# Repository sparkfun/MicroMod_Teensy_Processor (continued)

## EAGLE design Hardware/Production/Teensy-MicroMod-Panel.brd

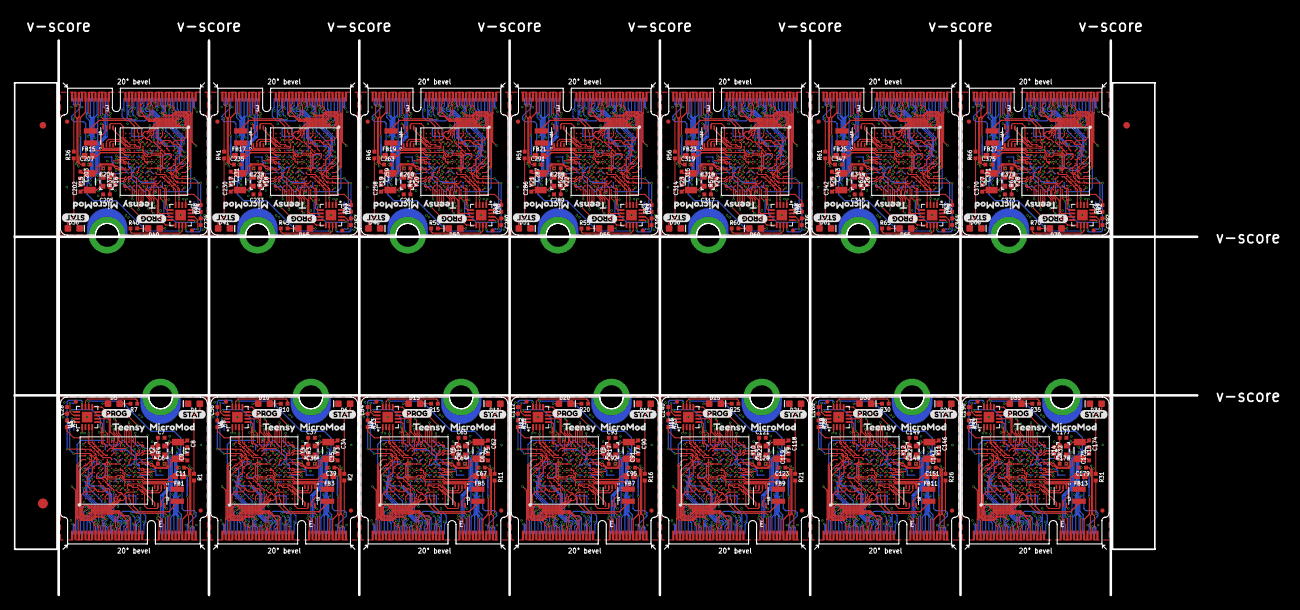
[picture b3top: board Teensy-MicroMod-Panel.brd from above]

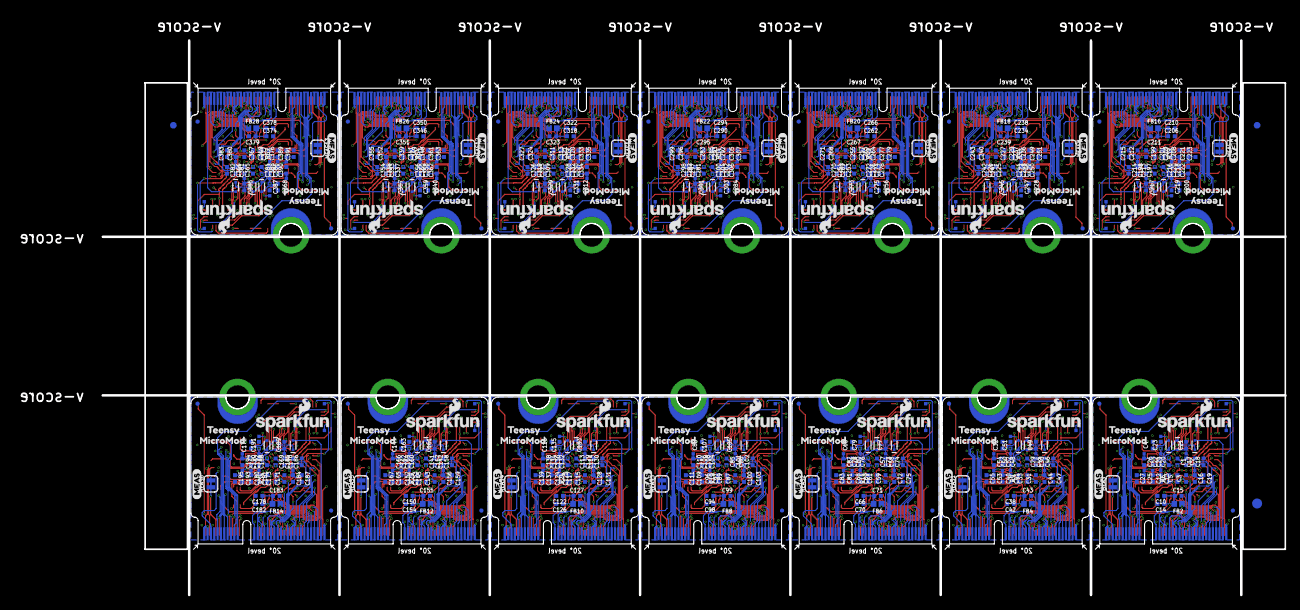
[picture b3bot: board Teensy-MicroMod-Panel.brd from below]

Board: 4 copper layers, 177.1 x 83.1 mm, 986 parts (619 on the bottom side), 1218 nets.

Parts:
C1, C11, C29, C39, C57, C67, C85, C95, C113, C123, C141, C151, C169, C179, C197, C207, C225, C235, C253, C263, C281, C291, C309, C319, C337, C347, C365, C375: 2.2uF; 0402-TIGHT
C2, C14, C18, C26, C27, C30, C42, C46, C54, C55, C58, C70, C74, C82, C83, C86, C98, C102, C110, C111, C114, C126, C130, C138, C139, C142, C154, C158, C166, C167, C170, C182, C186, C194, C195, C198, C210, C214, C222, C223, C226, C238, C242, C250, C251, C254, C266, C270, C278, C279, C282, C294, C298, C306, C307, C310, C322, C326, C334, C335, C338, C350, C354, C362, C363, C366, C378, C382, C390, C391: 4.7uF; 0402-TIGHT
C3, C4, C12, C13, C15, C17, C20, C22, C23, C24, C25, C28, C31, C32, C40, C41, C43, C45, C48, C50, C51, C52, C53, C56, C59, C60, C68, C69, C71, C73, C76, C78, C79, C80, C81, C84, C87, C88, C96, C97, C99, C101, C104, C106, C107, C108, C109, C112, C115, C116, C124, C125, C127, C129, C132, C134, C135, C136, C137, C140, C143, C144, C152, C153, C155, C157, C160, C162, C163, C164, C165, C168, C171, C172, C180, C181, C183, C185, C188, C190, C191, C192, C193, C196, C199, C200, C208, C209, C211, C213, C216, C218, C219, C220, C221, C224, C227, C228, C236, C237, C239, C241, C244, C246, C247, C248, C249, C252, C255, C256, C264, C265, C267, C269, C272, C274, C275, C276, C277, C280, C283, C284, C292, C293, C295, C297, C300, C302, C303, C304, C305, C308, C311, C312, C320, C321, C323, C325, C328, C330, C331, C332, C333, C336, C339, C340, C348, C349, C351, C353, C356, C358, C359, C360, C361, C364, C367, C368, C376, C377, C379, C381, C384, C386, C387, C388, C389, C392: 0.22uF; 0402-TIGHT
C5, C16, C33, C44, C61, C72, C89, C100, C117, C128, C145, C156, C173, C184, C201, C212, C229, C240, C257, C268, C285, C296, C313, C324, C341, C352, C369, C380: 10nF; 0402-TIGHT
C6, C7, C36, C37, C64, C65, C92, C93, C120, C121, C148, C149, C176, C177, C204, C205, C232, C233, C260, C261, C288, C289, C316, C317, C344, C345, C372, C373: 12pF; 0402-TIGHT
C8, C9, C34, C35, C62, C63, C90, C91, C118, C119, C146, C147, C174, C175, C202, C203, C230, C231, C258, C259, C286, C287, C314, C315, C342, C343, C370, C371: 20pF; 0402-TIGHT
C10, C19, C21, C38, C47, C49, C66, C75, C77, C94, C103, C105, C122, C131, C133, C150, C159, C161, C178, C187, C189, C206, C215, C217, C234, C243, C245, C262, C271, C273, C290, C299, C301, C318, C327, C329, C346, C355, C357, C374, C383, C385: 10uF; 0402-TIGHT
D1, D6, D11, D16, D21, D26, D31, D36, D41, D46, D51, D56, D61, D66: BLUE; LED-0603
D2, D7, D12, D17, D22, D27, D32, D37, D42, D47, D52, D57, D62, D67: 120mA370mV; SOD-523
D3, D4, D8, D9, D13, D14, D18, D19, D23, D24, D28, D29, D33, D34, D38, D39, D43, D44, D48, D49, D53, D54, D58, D59, D63, D64, D68, D69: 120mA/370mV; SOD-523
D5, D10, D15, D20, D25, D30, D35, D40, D45, D50, D55, D60, D65, D70: Yellow; LED-0603
E$1, E$2, E$3, E$4: FIDUCIAL-1X2
E$5, E$6: FIDUCIAL-1.5X3
FB1, FB2, FB3, FB4, FB5, FB6, FB7, FB8, FB9, FB10, FB11, FB12, FB13, FB14, FB15, FB16, FB17, FB18, FB19, FB20, FB21, FB22, FB23, FB24, FB25, FB26, FB27, FB28: 120Ω; 0402
FD1, FD2, FD3, FD4, FD5, FD6, FD7, FD8, FD9, FD10, FD11, FD12, FD13, FD14, FD15, FD16, FD17, FD18, FD19, FD20, FD21, FD22, FD23, FD24, FD25, FD26, FD27, FD28, FD29, FD30, FD31, FD32, FD33, FD34, FD35, FD36, FD37, FD38, FD39, FD40, FD41, FD42, FD43, FD44, FD45, FD46, FD47, FD48, FD49, FD50, FD51, FD52, FD53, FD54, FD55, FD56: FIDUCIALUFIDUCIAL; FIDUCIAL-MICRO
J1, J2, J3, J4, J5, J6, J7, J8, J9, J10, J11, J12, J13, J14: MICROMOD-2222; M.2-CARD-E-22
L1, L2, L3, L4, L5, L6, L7, L8, L9, L10, L11, L12, L13, L14: 4.7μH; 1008(2520)
LOGO1, LOGO2, LOGO3, LOGO4, LOGO5, LOGO6, LOGO7, LOGO8, LOGO9, LOGO10, LOGO11, LOGO12, LOGO13, LOGO14: SFE_LOGO_NAME_FLAME.1_INCH; SFE_LOGO_NAME_FLAME_.1
MEAS, MEAS1, MEAS2, MEAS3, MEAS4, MEAS5, MEAS6, MEAS7, MEAS8, MEAS9, MEAS10, MEAS11, MEAS12, MEAS13: SMT-JUMPER_2_NC_TRACE_SILK
R1, R2, R7, R10, R11, R15, R16, R20, R21, R25, R26, R30, R31, R35, R36, R40, R41, R45, R46, R50, R51, R55, R56, R60, R61, R65, R66, R70: 1k; 0402-TIGHT
R3, R4, R12, R17, R22, R27, R32, R37, R42, R47, R52, R57, R62, R67: 2.2M; 0402-TIGHT
R5, R6, R8, R9, R13, R14, R18, R19, R23, R24, R28, R29, R33, R34, R38, R39, R43, R44, R48, R49, R53, R54, R58, R59, R63, R64, R68, R69: 100k; 0402-TIGHT
TP1, TP2, TP21, TP31, TP41, TP51, TP61, TP71, TP81, TP91, TP101, TP111, TP121, TP131: 32kHz Test; PAD.02X.02
TP3, TP4, TP5, TP6, TP7, TP8, TP9, TP10, TP11, TP12, TP13, TP14, TP15, TP16, TP17, TP18, TP19, TP20, TP22, TP23, TP24, TP25, TP26, TP27, TP28, TP29, TP30, TP32, TP33, TP34, TP35, TP36, TP37, TP38, TP39, TP40, TP42, TP43, TP44, TP45, TP46, TP47, TP48, TP49, TP50, TP52, TP53, TP54, TP55, TP56, TP57, TP58, TP59, TP60, TP62, TP63, TP64, TP65, TP66, TP67, TP68, TP69, TP70, TP72, TP73, TP74, TP75, TP76, TP77, TP78, TP79, TP80, TP82, TP83, TP84, TP85, TP86, TP87, TP88, TP89, TP90, TP92, TP93, TP94, TP95, TP96, TP97, TP98, TP99, TP100, TP102, TP103, TP104, TP105, TP106, TP107, TP108, TP109, TP110, TP112, TP113, TP114, TP115, TP116, TP117, TP118, TP119, TP120, TP122, TP123, TP124, TP125, TP126, TP127, TP128, TP129, TP130, TP132, TP133, TP134, TP135, TP136, TP137, TP138, TP139, TP140: PAD.02X.02
U1, U4, U7, U10, U13, U16, U19, U22, U25, U28, U31, U34, U37, U40: IMXRT1062DV10X10; IMXRT1062
U2, U5, U8, U11, U14, U17, U20, U23, U26, U29, U32, U35, U38, U41: W25QXX; USON-8
U3, U6, U9, U12, U15, U18, U21, U24, U27, U30, U33, U36, U39, U42: MKL02Z32VFG4; QFN-16
U$1, U$3, U$9, U$12, U$16, U$19, U$23, U$26, U$30, U$33, U$37, U$40, U$44, U$47, U$51, U$54, U$58, U$61, U$65, U$68, U$72, U$75, U$79, U$82, U$86, U$89, U$93, U$96: TEENSY2
U$2, U$5, U$8, U$13, U$15, U$20, U$22, U$27, U$29, U$34, U$36, U$41, U$43, U$48, U$50, U$55, U$57, U$62, U$64, U$69, U$71, U$76, U$78, U$83, U$85, U$90, U$92, U$97: MICROMOD0
U$4, U$11, U$18, U$25, U$32, U$39, U$46, U$53, U$60, U$67, U$74, U$81, U$88, U$95: PROG_32
U$6, U$10, U$17, U$24, U$31, U$38, U$45, U$52, U$59, U$66, U$73, U$80, U$87, U$94: STAT_32
U$7, U$14, U$21, U$28, U$35, U$42, U$49, U$56, U$63, U$70, U$77, U$84, U$91, U$98: MEAS_32
Y1, Y3, Y5, Y7, Y9, Y11, Y13, Y15, Y17, Y19, Y21, Y23, Y25, Y27: 32.768kHz; CRYSTAL-SMD-3.2X1.5MM
Y2, Y4, Y6, Y8, Y10, Y12, Y14, Y16, Y18, Y20, Y22, Y24, Y26, Y28: 24MHz; CRYSTAL-SMD-2.0X1.6MM

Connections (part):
3.3V: C1.1, C2.1, C3.1, C4.1, C5.1, C28.1, D2.A, D5.A, FB2.1, J1.2, J1.4, J1.74, R6.1, U1.E6, U1.E9, U1.F5, U1.F10, U1.J6, U1.J10, U1.K4, U1.K5, U1.N14, U1.P12, U2.8, U3.1
3.3V1: C29.1, C30.1, C31.1, C32.1, C33.1, C56.1, D7.A, D10.A, FB4.1, J2.2, J2.4, J2.74, R9.1, U4.E6, U4.E9, U4.F5, U4.F10, U4.J6, U4.J10, U4.K4, U4.K5, U4.N14, U4.P12, U5.8, U6.1
3.3V2: C57.1, C58.1, C59.1, C60.1, C61.1, C84.1, D12.A, D15.A, FB6.1, J3.2, J3.4, J3.74, R14.1, U7.E6, U7.E9, U7.F5, U7.F10, U7.J6, U7.J10, U7.K4, U7.K5, U7.N14, U7.P12, U8.8, U9.1
3.3V3: C85.1, C86.1, C87.1, C88.1, C89.1, C112.1, D17.A, D20.A, FB8.1, J4.2, J4.4, J4.74, R19.1, U10.E6, U10.E9, U10.F5, U10.F10, U10.J6, U10.J10, U10.K4, U10.K5, U10.N14, U10.P12, U11.8, U12.1
3.3V4: C113.1, C114.1, C115.1, C116.1, C117.1, C140.1, D22.A, D25.A, FB10.1, J5.2, J5.4, J5.74, R24.1, U13.E6, U13.E9, U13.F5, U13.F10, U13.J6, U13.J10, U13.K4, U13.K5, U13.N14, U13.P12, U14.8, U15.1
3.3V5: C141.1, C142.1, C143.1, C144.1, C145.1, C168.1, D27.A, D30.A, FB12.1, J6.2, J6.4, J6.74, R29.1, U16.E6, U16.E9, U16.F5, U16.F10, U16.J6, U16.J10, U16.K4, U16.K5, U16.N14, U16.P12, U17.8, U18.1
3.3V6: C169.1, C170.1, C171.1, C172.1, C173.1, C196.1, D32.A, D35.A, FB14.1, J7.2, J7.4, J7.74, R34.1, U19.E6, U19.E9, U19.F5, U19.F10, U19.J6, U19.J10, U19.K4, U19.K5, U19.N14, U19.P12, U20.8, U21.1
3.3V7: C197.1, C198.1, C199.1, C200.1, C201.1, C224.1, D37.A, D40.A, FB16.1, J8.2, J8.4, J8.74, R39.1, U22.E6, U22.E9, U22.F5, U22.F10, U22.J6, U22.J10, U22.K4, U22.K5, U22.N14, U22.P12, U23.8, U24.1
3.3V8: C225.1, C226.1, C227.1, C228.1, C229.1, C252.1, D42.A, D45.A, FB18.1, J9.2, J9.4, J9.74, R44.1, U25.E6, U25.E9, U25.F5, U25.F10, U25.J6, U25.J10, U25.K4, U25.K5, U25.N14, U25.P12, U26.8, U27.1
3.3V9: C253.1, C254.1, C255.1, C256.1, C257.1, C280.1, D47.A, D50.A, FB20.1, J10.2, J10.4, J10.74, R49.1, U28.E6, U28.E9, U28.F5, U28.F10, U28.J6, U28.J10, U28.K4, U28.K5, U28.N14, U28.P12, U29.8, U30.1
3.3V10: C281.1, C282.1, C283.1, C284.1, C285.1, C308.1, D52.A, D55.A, FB22.1, J11.2, J11.4, J11.74, R54.1, U31.E6, U31.E9, U31.F5, U31.F10, U31.J6, U31.J10, U31.K4, U31.K5, U31.N14, U31.P12, U32.8, U33.1
3.3V11: C309.1, C310.1, C311.1, C312.1, C313.1, C336.1, D57.A, D60.A, FB24.1, J12.2, J12.4, J12.74, R59.1, U34.E6, U34.E9, U34.F5, U34.F10, U34.J6, U34.J10, U34.K4, U34.K5, U34.N14, U34.P12, U35.8, U36.1
3.3V12: C337.1, C338.1, C339.1, C340.1, C341.1, C364.1, D62.A, D65.A, FB26.1, J13.2, J13.4, J13.74, R64.1, U37.E6, U37.E9, U37.F5, U37.F10, U37.J6, U37.J10, U37.K4, U37.K5, U37.N14, U37.P12, U38.8, U39.1
3.3V13: C365.1, C366.1, C367.1, C368.1, C369.1, C392.1, D67.A, D70.A, FB28.1, J14.2, J14.4, J14.74, R69.1, U40.E6, U40.E9, U40.F5, U40.F10, U40.J6, U40.J10, U40.K4, U40.K5, U40.N14, U40.P12, U41.8, U42.1
34/DAT1: J1.66, U1.K1
34/DAT2: J2.66, U4.K1
34/DAT3: J3.66, U7.K1
34/DAT4: J4.66, U10.K1
34/DAT5: J5.66, U13.K1
34/DAT6: J6.66, U16.K1
34/DAT7: J7.66, U19.K1
34/DAT8: J8.66, U22.K1
34/DAT9: J9.66, U25.K1
34/DAT10: J10.66, U28.K1
34/DAT11: J11.66, U31.K1
34/DAT12: J12.66, U34.K1
34/DAT13: J13.66, U37.K1
34/DAT14: J14.66, U40.K1
35/DAT0: J1.64, U1.J1
35/DAT1: J2.64, U4.J1
35/DAT2: J3.64, U7.J1
35/DAT3: J4.64, U10.J1
35/DAT4: J5.64, U13.J1
35/DAT5: J6.64, U16.J1
35/DAT6: J7.64, U19.J1
35/DAT7: J8.64, U22.J1
35/DAT8: J9.64, U25.J1
35/DAT9: J10.64, U28.J1
35/DAT10: J11.64, U31.J1
35/DAT11: J12.64, U34.J1
35/DAT12: J13.64, U37.J1
35/DAT13: J14.64, U40.J1
36/CLK: J1.60, U1.J3
36/CLK1: J2.60, U4.J3
36/CLK2: J3.60, U7.J3
36/CLK3: J4.60, U10.J3
36/CLK4: J5.60, U13.J3
36/CLK5: J6.60, U16.J3
36/CLK6: J7.60, U19.J3
36/CLK7: J8.60, U22.J3
36/CLK8: J9.60, U25.J3
36/CLK9: J10.60, U28.J3
36/CLK10: J11.60, U31.J3
36/CLK11: J12.60, U34.J3
36/CLK12: J13.60, U37.J3
36/CLK13: J14.60, U40.J3
37/CMD: J1.62, U1.J4
37/CMD1: J2.62, U4.J4
37/CMD2: J3.62, U7.J4
37/CMD3: J4.62, U10.J4
37/CMD4: J5.62, U13.J4
37/CMD5: J6.62, U16.J4
37/CMD6: J7.62, U19.J4
37/CMD7: J8.62, U22.J4
37/CMD8: J9.62, U25.J4
37/CMD9: J10.62, U28.J4
37/CMD10: J11.62, U31.J4
37/CMD11: J12.62, U34.J4
37/CMD12: J13.62, U37.J4
37/CMD13: J14.62, U40.J4
38/DAT1: J2.70, U4.H2
38/DAT2: J3.70, U7.H2
38/DAT3: J1.70, U1.H2
38/DAT4: J4.70, U10.H2
38/DAT5: J5.70, U13.H2
38/DAT6: J6.70, U16.H2
38/DAT7: J7.70, U19.H2
38/DAT8: J8.70, U22.H2
38/DAT9: J9.70, U25.H2
38/DAT10: J10.70, U28.H2
38/DAT11: J11.70, U31.H2
38/DAT12: J12.70, U34.H2
38/DAT13: J13.70, U37.H2
38/DAT14: J14.70, U40.H2
39/DAT1: J2.68, U4.J2
39/DAT2: J1.68, U1.J2
39/DAT3: J3.68, U7.J2
39/DAT4: J4.68, U10.J2
39/DAT5: J5.68, U13.J2
39/DAT6: J6.68, U16.J2
39/DAT7: J7.68, U19.J2
39/DAT8: J8.68, U22.J2
39/DAT9: J9.68, U25.J2
39/DAT10: J10.68, U28.J2
39/DAT11: J11.68, U31.J2
39/DAT12: J12.68, U34.J2
39/DAT13: J13.68, U37.J2
39/DAT14: J14.68, U40.J2
ADC1ST/14/A0: J1.34, U1.L11
ADC1ST/14/A1: J2.34, U4.L11
ADC1ST/14/A2: J3.34, U7.L11
ADC1ST/14/A3: J4.34, U10.L11
ADC1ST/14/A4: J5.34, U13.L11
ADC1ST/14/A5: J6.34, U16.L11
ADC1ST/14/A6: J7.34, U19.L11
ADC1ST/14/A7: J8.34, U22.L11
ADC1ST/14/A8: J9.34, U25.L11
ADC1ST/14/A9: J10.34, U28.L11
ADC1ST/14/A10: J11.34, U31.L11
ADC1ST/14/A11: J12.34, U34.L11
ADC1ST/14/A12: J13.34, U37.L11
ADC1ST/14/A13: J14.34, U40.L11
ADC2ND/15/A1: J1.38, U1.M12
ADC2ND/15/A2: J2.38, U4.M12
ADC2ND/15/A3: J3.38, U7.M12
ADC2ND/15/A4: J4.38, U10.M12
ADC2ND/15/A5: J5.38, U13.M12
ADC2ND/15/A6: J6.38, U16.M12
ADC2ND/15/A7: J7.38, U19.M12
ADC2ND/15/A8: J8.38, U22.M12
ADC2ND/15/A9: J9.38, U25.M12
ADC2ND/15/A10: J10.38, U28.M12
ADC2ND/15/A11: J11.38, U31.M12
ADC2ND/15/A12: J12.38, U34.M12
ADC2ND/15/A13: J13.38, U37.M12
ADC2ND/15/A14: J14.38, U40.M12
AUD_IN/1: J2.54, U4.A11
AUD_IN/2: J3.54, U7.A11
AUD_IN/3: J4.54, U10.A11
AUD_IN/4: J5.54, U13.A11
AUD_IN/5: J6.54, U16.A11
AUD_IN/6: J7.54, U19.A11
AUD_IN/7: J8.54, U22.A11
AUD_IN/8: J1.54, U1.A11
AUD_IN/9: J9.54, U25.A11
AUD_IN/10: J10.54, U28.A11
AUD_IN/11: J11.54, U31.A11
AUD_IN/12: J12.54, U34.A11
AUD_IN/13: J13.54, U37.A11
AUD_IN/14: J14.54, U40.A11
AUD_OUT/1: J2.56, U4.B11
AUD_OUT/2: J3.56, U7.B11
AUD_OUT/3: J4.56, U10.B11
AUD_OUT/4: J5.56, U13.B11
AUD_OUT/5: J6.56, U16.B11
AUD_OUT/6: J7.56, U19.B11
AUD_OUT/7: J1.56, U1.B11
AUD_OUT/8: J8.56, U22.B11
AUD_OUT/9: J9.56, U25.B11
AUD_OUT/10: J10.56, U28.B11
AUD_OUT/11: J11.56, U31.B11
AUD_OUT/12: J12.56, U34.B11
AUD_OUT/13: J13.56, U37.B11
AUD_OUT/14: J14.56, U40.B11
BATT_VIN/22/A1: J2.51, U4.H13
BATT_VIN/22/A2: J3.51, U7.H13
BATT_VIN/22/A3: J4.51, U10.H13
BATT_VIN/22/A4: J5.51, U13.H13
BATT_VIN/22/A5: J6.51, U16.H13
BATT_VIN/22/A6: J7.51, U19.H13
BATT_VIN/22/A7: J8.51, U22.H13
BATT_VIN/22/A8: J1.51, U1.H13
BATT_VIN/22/A9: J9.51, U25.H13
BATT_VIN/22/A10: J10.51, U28.H13
BATT_VIN/22/A11: J11.51, U31.H13
BATT_VIN/22/A12: J12.51, U34.H13
BATT_VIN/22/A13: J13.51, U37.H13
BATT_VIN/22/A14: J14.51, U40.H13
BCLK/21/A1: J2.50, U4.J13
BCLK/21/A2: J3.50, U7.J13
BCLK/21/A3: J4.50, U10.J13
BCLK/21/A4: J5.50, U13.J13
BCLK/21/A5: J6.50, U16.J13
BCLK/21/A6: J7.50, U19.J13
BCLK/21/A7: J1.50, U1.J13
BCLK/21/A8: J8.50, U22.J13
BCLK/21/A9: J9.50, U25.J13
BCLK/21/A10: J10.50, U28.J13
BCLK/21/A11: J11.50, U31.J13
BCLK/21/A12: J12.50, U34.J13
BCLK/21/A13: J13.50, U37.J13
BCLK/21/A14: J14.50, U40.J13
BOOTMODE0: U1.F11, U3.4
BOOTMODE1: U4.F11, U6.4
BOOTMODE2: U7.F11, U9.4
BOOTMODE3: U10.F11, U12.4
BOOTMODE4: U13.F11, U15.4
BOOTMODE5: U16.F11, U18.4
BOOTMODE6: U19.F11, U21.4
BOOTMODE7: U22.F11, U24.4
BOOTMODE8: U25.F11, U27.4
BOOTMODE9: U28.F11, U30.4
BOOTMODE10: U31.F11, U33.4
BOOTMODE11: U34.F11, U36.4
BOOTMODE12: U37.F11, U39.4
BOOTMODE13: U40.F11, U42.4
CAN_RX/1: J2.41, U4.E4
CAN_RX/2: J3.41, U7.E4
CAN_RX/3: J4.41, U10.E4
CAN_RX/4: J5.41, U13.E4
CAN_RX/5: J6.41, U16.E4
CAN_RX/6: J7.41, U19.E4
CAN_RX/7: J8.41, U22.E4
CAN_RX/8: J9.41, U25.E4
CAN_RX/9: J10.41, U28.E4
CAN_RX/10: J11.41, U31.E4
CAN_RX/11: J12.41, U34.E4
CAN_RX/12: J13.41, U37.E4
CAN_RX/13: J14.41, U40.E4
CAN_RX/30: J1.41, U1.E4
CAN_TX/1: J2.43, U4.C3
CAN_TX/2: J3.43, U7.C3
CAN_TX/3: J4.43, U10.C3
CAN_TX/4: J5.43, U13.C3
CAN_TX/5: J6.43, U16.C3
CAN_TX/6: J7.43, U19.C3
CAN_TX/7: J8.43, U22.C3
CAN_TX/8: J9.43, U25.C3
CAN_TX/9: J10.43, U28.C3
CAN_TX/10: J11.43, U31.C3
CAN_TX/11: J12.43, U34.C3
CAN_TX/12: J13.43, U37.C3
CAN_TX/13: J14.43, U40.C3
CAN_TX/31: J1.43, U1.C3
CS/1: J2.49, U4.D7
CS/2: J3.49, U7.D7
CS/3: J4.49, U10.D7
CS/4: J5.49, U13.D7
CS/5: J6.49, U16.D7
CS/6: J7.49, U19.D7
CS/7: J8.49, U22.D7
CS/8: J9.49, U25.D7
CS/9: J10.49, U28.D7
CS/10: J1.49, U1.D7
CS/11: J11.49, U31.D7
CS/12: J12.49, U34.D7
CS/13: J13.49, U37.D7
CS/14: J14.49, U40.D7
DEBUG_EN: U1.F3, U3.15
DEBUG_EN1: U4.F3, U6.15
DEBUG_EN2: U7.F3, U9.15
DEBUG_EN3: U10.F3, U12.15
DEBUG_EN4: U13.F3, U15.15
DEBUG_EN5: U16.F3, U18.15
DEBUG_EN6: U19.F3, U21.15
DEBUG_EN7: U22.F3, U24.15
DEBUG_EN8: U25.F3, U27.15
DEBUG_EN9: U28.F3, U30.15
DEBUG_EN10: U31.F3, U33.15
DEBUG_EN11: U34.F3, U36.15
DEBUG_EN12: U37.F3, U39.15
DEBUG_EN13: U40.F3, U42.15
DEBUG_SWO: U1.D10, U3.12
DEBUG_SWO1: U4.D10, U6.12
DEBUG_SWO2: U7.D10, U9.12
DEBUG_SWO3: U10.D10, U12.12
DEBUG_SWO4: U13.D10, U15.12
DEBUG_SWO5: U16.D10, U18.12
DEBUG_SWO6: U19.D10, U21.12
DEBUG_SWO7: U22.D10, U24.12
DEBUG_SWO8: U25.D10, U27.12
DEBUG_SWO9: U28.D10, U30.12
DEBUG_SWO10: U31.D10, U33.12
DEBUG_SWO11: U34.D10, U36.12
DEBUG_SWO12: U37.D10, U39.12
DEBUG_SWO13: U40.D10, U42.12
GND: C1.2, C2.2, C3.2, C4.2, C5.2, C6.2, C7.2, C8.2, C9.2, C10.2, C11.2, C12.2, C13.2, C14.2, C15.2, C16.2, C17.2, C18.2, C19.2, C20.2, C21.2, C22.2, C23.2, C24.2, C25.2, C26.2, C27.2, C28.2, D1.C, J1.1, J1.7, J1.33, J1.36, J1.39, J1.45, J1.75, J1.GND, J1.GND-SM-B, R4.1, R5.1, U1.A1, U1.A14, U1.B5, U1.B10, U1.E2, U1.E13, U1.G7, U1.G8, U1.G14, U1.H7, U1.H8, U1.J7, U1.J8, U1.K2, U1.K6, U1.K9, U1.K13, U1.L9, U1.N1, U1.N2, U1.N5, U1.N8, U1.P1, U1.P14, U2.4, U3.2, U3.17
GND1: C29.2, C30.2, C31.2, C32.2, C33.2, C34.2, C35.2, C36.2, C37.2, C38.2, C39.2, C40.2, C41.2, C42.2, C43.2, C44.2, C45.2, C46.2, C47.2, C48.2, C49.2, C50.2, C51.2, C52.2, C53.2, C54.2, C55.2, C56.2, D6.C, J2.1, J2.7, J2.33, J2.36, J2.39, J2.45, J2.75, J2.GND, J2.GND-SM-B, R3.1, R8.1, U4.A1, U4.A14, U4.B5, U4.B10, U4.E2, U4.E13, U4.G7, U4.G8, U4.G14, U4.H7, U4.H8, U4.J7, U4.J8, U4.K2, U4.K6, U4.K9, U4.K13, U4.L9, U4.N1, U4.N2, U4.N5, U4.N8, U4.P1, U4.P14, U5.4, U6.2, U6.17
GND2: C57.2, C58.2, C59.2, C60.2, C61.2, C62.2, C63.2, C64.2, C65.2, C66.2, C67.2, C68.2, C69.2, C70.2, C71.2, C72.2, C73.2, C74.2, C75.2, C76.2, C77.2, C78.2, C79.2, C80.2, C81.2, C82.2, C83.2, C84.2, D11.C, J3.1, J3.7, J3.33, J3.36, J3.39, J3.45, J3.75, J3.GND, J3.GND-SM-B, R12.1, R13.1, U7.A1, U7.A14, U7.B5, U7.B10, U7.E2, U7.E13, U7.G7, U7.G8, U7.G14, U7.H7, U7.H8, U7.J7, U7.J8, U7.K2, U7.K6, U7.K9, U7.K13, U7.L9, U7.N1, U7.N2, U7.N5, U7.N8, U7.P1, U7.P14, U8.4, U9.2, U9.17
GND3: C85.2, C86.2, C87.2, C88.2, C89.2, C90.2, C91.2, C92.2, C93.2, C94.2, C95.2, C96.2, C97.2, C98.2, C99.2, C100.2, C101.2, C102.2, C103.2, C104.2, C105.2, C106.2, C107.2, C108.2, C109.2, C110.2, C111.2, C112.2, D16.C, J4.1, J4.7, J4.33, J4.36, J4.39, J4.45, J4.75, J4.GND, J4.GND-SM-B, R17.1, R18.1, U10.A1, U10.A14, U10.B5, U10.B10, U10.E2, U10.E13, U10.G7, U10.G8, U10.G14, U10.H7, U10.H8, U10.J7, U10.J8, U10.K2, U10.K6, U10.K9, U10.K13, U10.L9, U10.N1, U10.N2, U10.N5, U10.N8, U10.P1, U10.P14, U11.4, U12.2, U12.17
GND4: C113.2, C114.2, C115.2, C116.2, C117.2, C118.2, C119.2, C120.2, C121.2, C122.2, C123.2, C124.2, C125.2, C126.2, C127.2, C128.2, C129.2, C130.2, C131.2, C132.2, C133.2, C134.2, C135.2, C136.2, C137.2, C138.2, C139.2, C140.2, D21.C, J5.1, J5.7, J5.33, J5.36, J5.39, J5.45, J5.75, J5.GND, J5.GND-SM-B, R22.1, R23.1, U13.A1, U13.A14, U13.B5, U13.B10, U13.E2, U13.E13, U13.G7, U13.G8, U13.G14, U13.H7, U13.H8, U13.J7, U13.J8, U13.K2, U13.K6, U13.K9, U13.K13, U13.L9, U13.N1, U13.N2, U13.N5, U13.N8, U13.P1, U13.P14, U14.4, U15.2, U15.17
GND5: C141.2, C142.2, C143.2, C144.2, C145.2, C146.2, C147.2, C148.2, C149.2, C150.2, C151.2, C152.2, C153.2, C154.2, C155.2, C156.2, C157.2, C158.2, C159.2, C160.2, C161.2, C162.2, C163.2, C164.2, C165.2, C166.2, C167.2, C168.2, D26.C, J6.1, J6.7, J6.33, J6.36, J6.39, J6.45, J6.75, J6.GND, J6.GND-SM-B, R27.1, R28.1, U16.A1, U16.A14, U16.B5, U16.B10, U16.E2, U16.E13, U16.G7, U16.G8, U16.G14, U16.H7, U16.H8, U16.J7, U16.J8, U16.K2, U16.K6, U16.K9, U16.K13, U16.L9, U16.N1, U16.N2, U16.N5, U16.N8, U16.P1, U16.P14, U17.4, U18.2, U18.17
GND6: C169.2, C170.2, C171.2, C172.2, C173.2, C174.2, C175.2, C176.2, C177.2, C178.2, C179.2, C180.2, C181.2, C182.2, C183.2, C184.2, C185.2, C186.2, C187.2, C188.2, C189.2, C190.2, C191.2, C192.2, C193.2, C194.2, C195.2, C196.2, D31.C, J7.1, J7.7, J7.33, J7.36, J7.39, J7.45, J7.75, J7.GND, J7.GND-SM-B, R32.1, R33.1, U19.A1, U19.A14, U19.B5, U19.B10, U19.E2, U19.E13, U19.G7, U19.G8, U19.G14, U19.H7, U19.H8, U19.J7, U19.J8, U19.K2, U19.K6, U19.K9, U19.K13, U19.L9, U19.N1, U19.N2, U19.N5, U19.N8, U19.P1, U19.P14, U20.4, U21.2, U21.17
GND7: C197.2, C198.2, C199.2, C200.2, C201.2, C202.2, C203.2, C204.2, C205.2, C206.2, C207.2, C208.2, C209.2, C210.2, C211.2, C212.2, C213.2, C214.2, C215.2, C216.2, C217.2, C218.2, C219.2, C220.2, C221.2, C222.2, C223.2, C224.2, D36.C, J8.1, J8.7, J8.33, J8.36, J8.39, J8.45, J8.75, J8.GND, J8.GND-SM-B, R37.1, R38.1, U22.A1, U22.A14, U22.B5, U22.B10, U22.E2, U22.E13, U22.G7, U22.G8, U22.G14, U22.H7, U22.H8, U22.J7, U22.J8, U22.K2, U22.K6, U22.K9, U22.K13, U22.L9, U22.N1, U22.N2, U22.N5, U22.N8, U22.P1, U22.P14, U23.4, U24.2, U24.17
GND8: C225.2, C226.2, C227.2, C228.2, C229.2, C230.2, C231.2, C232.2, C233.2, C234.2, C235.2, C236.2, C237.2, C238.2, C239.2, C240.2, C241.2, C242.2, C243.2, C244.2, C245.2, C246.2, C247.2, C248.2, C249.2, C250.2, C251.2, C252.2, D41.C, J9.1, J9.7, J9.33, J9.36, J9.39, J9.45, J9.75, J9.GND, J9.GND-SM-B, R42.1, R43.1, U25.A1, U25.A14, U25.B5, U25.B10, U25.E2, U25.E13, U25.G7, U25.G8, U25.G14, U25.H7, U25.H8, U25.J7, U25.J8, U25.K2, U25.K6, U25.K9, U25.K13, U25.L9, U25.N1, U25.N2, U25.N5, U25.N8, U25.P1, U25.P14, U26.4, U27.2, U27.17
GND9: C253.2, C254.2, C255.2, C256.2, C257.2, C258.2, C259.2, C260.2, C261.2, C262.2, C263.2, C264.2, C265.2, C266.2, C267.2, C268.2, C269.2, C270.2, C271.2, C272.2, C273.2, C274.2, C275.2, C276.2, C277.2, C278.2, C279.2, C280.2, D46.C, J10.1, J10.7, J10.33, J10.36, J10.39, J10.45, J10.75, J10.GND, J10.GND-SM-B, R47.1, R48.1, U28.A1, U28.A14, U28.B5, U28.B10, U28.E2, U28.E13, U28.G7, U28.G8, U28.G14, U28.H7, U28.H8, U28.J7, U28.J8, U28.K2, U28.K6, U28.K9, U28.K13, U28.L9, U28.N1, U28.N2, U28.N5, U28.N8, U28.P1, U28.P14, U29.4, U30.2, U30.17
GND10: C281.2, C282.2, C283.2, C284.2, C285.2, C286.2, C287.2, C288.2, C289.2, C290.2, C291.2, C292.2, C293.2, C294.2, C295.2, C296.2, C297.2, C298.2, C299.2, C300.2, C301.2, C302.2, C303.2, C304.2, C305.2, C306.2, C307.2, C308.2, D51.C, J11.1, J11.7, J11.33, J11.36, J11.39, J11.45, J11.75, J11.GND, J11.GND-SM-B, R52.1, R53.1, U31.A1, U31.A14, U31.B5, U31.B10, U31.E2, U31.E13, U31.G7, U31.G8, U31.G14, U31.H7, U31.H8, U31.J7, U31.J8, U31.K2, U31.K6, U31.K9, U31.K13, U31.L9, U31.N1, U31.N2, U31.N5, U31.N8, U31.P1, U31.P14, U32.4, U33.2, U33.17
GND11: C309.2, C310.2, C311.2, C312.2, C313.2, C314.2, C315.2, C316.2, C317.2, C318.2, C319.2, C320.2, C321.2, C322.2, C323.2, C324.2, C325.2, C326.2, C327.2, C328.2, C329.2, C330.2, C331.2, C332.2, C333.2, C334.2, C335.2, C336.2, D56.C, J12.1, J12.7, J12.33, J12.36, J12.39, J12.45, J12.75, J12.GND, J12.GND-SM-B, R57.1, R58.1, U34.A1, U34.A14, U34.B5, U34.B10, U34.E2, U34.E13, U34.G7, U34.G8, U34.G14, U34.H7, U34.H8, U34.J7, U34.J8, U34.K2, U34.K6, U34.K9, U34.K13, U34.L9, U34.N1, U34.N2, U34.N5, U34.N8, U34.P1, U34.P14, U35.4, U36.2, U36.17
GND12: C337.2, C338.2, C339.2, C340.2, C341.2, C342.2, C343.2, C344.2, C345.2, C346.2, C347.2, C348.2, C349.2, C350.2, C351.2, C352.2, C353.2, C354.2, C355.2, C356.2, C357.2, C358.2, C359.2, C360.2, C361.2, C362.2, C363.2, C364.2, D61.C, J13.1, J13.7, J13.33, J13.36, J13.39, J13.45, J13.75, J13.GND, J13.GND-SM-B, R62.1, R63.1, U37.A1, U37.A14, U37.B5, U37.B10, U37.E2, U37.E13, U37.G7, U37.G8, U37.G14, U37.H7, U37.H8, U37.J7, U37.J8, U37.K2, U37.K6, U37.K9, U37.K13, U37.L9, U37.N1, U37.N2, U37.N5, U37.N8, U37.P1, U37.P14, U38.4, U39.2, U39.17
GND13: C365.2, C366.2, C367.2, C368.2, C369.2, C370.2, C371.2, C372.2, C373.2, C374.2, C375.2, C376.2, C377.2, C378.2, C379.2, C380.2, C381.2, C382.2, C383.2, C384.2, C385.2, C386.2, C387.2, C388.2, C389.2, C390.2, C391.2, C392.2, D66.C, J14.1, J14.7, J14.33, J14.36, J14.39, J14.45, J14.75, J14.GND, J14.GND-SM-B, R67.1, R68.1, U40.A1, U40.A14, U40.B5, U40.B10, U40.E2, U40.E13, U40.G7, U40.G8, U40.G14, U40.H7, U40.H8, U40.J7, U40.J8, U40.K2, U40.K6, U40.K9, U40.K13, U40.L9, U40.N1, U40.N2, U40.N5, U40.N8, U40.P1, U40.P14, U41.4, U42.2, U42.17
GPIO/1: J2.71, U4.A10
GPIO/2: J2.40, U4.D9
GPIO/3: J2.46, U4.D5
GPIO/4: J2.48, U4.C10
GPIO/5: J2.73, U4.H4
GPIO/6: J1.40, U1.D9
GPIO/7: J3.71, U7.A10
GPIO/8: J3.40, U7.D9
GPIO/9: J1.71, U1.A10
GPIO/10: J3.46, U7.D5
GPIO/11: J3.48, U7.C10
GPIO/12: J3.73, U7.H4
GPIO/13: J4.71, U10.A10
GPIO/14: J4.40, U10.D9
GPIO/15: J4.46, U10.D5
GPIO/16: J4.48, U10.C10
GPIO/17: J4.73, U10.H4
GPIO/18: J5.71, U13.A10
GPIO/19: J5.40, U13.D9
GPIO/20: J5.46, U13.D5
GPIO/21: J5.48, U13.C10
GPIO/22: J5.73, U13.H4
GPIO/23: J6.71, U16.A10
GPIO/24: J6.40, U16.D9
GPIO/25: J6.46, U16.D5
GPIO/26: J6.48, U16.C10
GPIO/26/A1: J2.42, U4.G12
GPIO/26/A2: J3.42, U7.G12
GPIO/26/A3: J4.42, U10.G12
GPIO/26/A4: J5.42, U13.G12
GPIO/26/A5: J6.42, U16.G12
GPIO/26/A6: J7.42, U19.G12
GPIO/26/A7: J8.42, U22.G12
GPIO/26/A8: J9.42, U25.G12
GPIO/26/A9: J10.42, U28.G12
GPIO/26/A10: J11.42, U31.G12
GPIO/26/A11: J12.42, U34.G12
GPIO/26/A12: J1.42, U1.G12
GPIO/26/A13: J13.42, U37.G12
GPIO/26/A14: J14.42, U40.G12
GPIO/27: J6.73, U16.H4
GPIO/27/A1: J2.44, U4.J14
GPIO/27/A2: J3.44, U7.J14
GPIO/27/A3: J4.44, U10.J14
GPIO/27/A4: J5.44, U13.J14
GPIO/27/A5: J6.44, U16.J14
GPIO/27/A6: J7.44, U19.J14
GPIO/27/A7: J8.44, U22.J14
GPIO/27/A8: J9.44, U25.J14
GPIO/27/A9: J10.44, U28.J14
GPIO/27/A10: J11.44, U31.J14
GPIO/27/A11: J12.44, U34.J14
GPIO/27/A12: J13.44, U37.J14
GPIO/27/A13: J1.44, U1.J14
GPIO/27/A14: J14.44, U40.J14
GPIO/28: J1.46, U1.D5
GPIO/29: J7.71, U19.A10
GPIO/30: J7.40, U19.D9
GPIO/31: J7.46, U19.D5
GPIO/32: J1.48, U1.C10
GPIO/33: J1.73, U1.H4
GPIO/34: J7.48, U19.C10
GPIO/35: J7.73, U19.H4
GPIO/36: J8.71, U22.A10
GPIO/37: J8.40, U22.D9
GPIO/38: J8.46, U22.D5
GPIO/39: J8.48, U22.C10
GPIO/40: J8.73, U22.H4
GPIO/41: J9.71, U25.A10
GPIO/42: J9.40, U25.D9
GPIO/43: J9.46, U25.D5
GPIO/44: J9.48, U25.C10
GPIO/45: J9.73, U25.H4
GPIO/46: J10.71, U28.A10
GPIO/47: J10.40, U28.D9
GPIO/48: J10.46, U28.D5
GPIO/49: J10.48, U28.C10
GPIO/50: J10.73, U28.H4
GPIO/51: J11.71, U31.A10
GPIO/52: J11.40, U31.D9
GPIO/53: J11.46, U31.D5
GPIO/54: J11.48, U31.C10
GPIO/55: J11.73, U31.H4
GPIO/56: J12.71, U34.A10
GPIO/57: J12.40, U34.D9
GPIO/58: J12.46, U34.D5
GPIO/59: J12.48, U34.C10
GPIO/60: J12.73, U34.H4
GPIO/61: J13.71, U37.A10
GPIO/62: J13.40, U37.D9
GPIO/63: J13.46, U37.D5
GPIO/64: J13.48, U37.C10
GPIO/65: J13.73, U37.H4
GPIO/66: J14.71, U40.A10
GPIO/67: J14.40, U40.D9
GPIO/68: J14.46, U40.D5
GPIO/69: J14.48, U40.C10
GPIO/70: J14.73, U40.H4
GPIO_1ST/1: J2.10, U4.H5
GPIO_1ST/2: J3.10, U7.H5
GPIO_1ST/3: J4.10, U10.H5
GPIO_1ST/4: J1.10, U1.H5
GPIO_1ST/5: J5.10, U13.H5
GPIO_1ST/6: J6.10, U16.H5
GPIO_1ST/7: J7.10, U19.H5
GPIO_1ST/8: J8.10, U22.H5
GPIO_1ST/9: J9.10, U25.H5
GPIO_1ST/10: J10.10, U28.H5
GPIO_1ST/11: J11.10, U31.H5
GPIO_1ST/12: J12.10, U34.H5
GPIO_1ST/13: J13.10, U37.H5
GPIO_1ST/14: J14.10, U40.H5
GPIO_2ND/1: J2.18, U4.H3
GPIO_2ND/2: J3.18, U7.H3
GPIO_2ND/3: J4.18, U10.H3
GPIO_2ND/4: J5.18, U13.H3
GPIO_2ND/5: J1.18, U1.H3
GPIO_2ND/6: J6.18, U16.H3
GPIO_2ND/7: J7.18, U19.H3
GPIO_2ND/8: J8.18, U22.H3
GPIO_2ND/9: J9.18, U25.H3
GPIO_2ND/10: J10.18, U28.H3
GPIO_2ND/11: J11.18, U31.H3
GPIO_2ND/12: J12.18, U34.H3
GPIO_2ND/13: J13.18, U37.H3
GPIO_2ND/14: J14.18, U40.H3
I2C_!INT!/1: J2.16, U4.C5
I2C_!INT!/2: J3.16, U7.C5
I2C_!INT!/3: J4.16, U10.C5
I2C_!INT!/4: J5.16, U13.C5
I2C_!INT!/5: J6.16, U16.C5
I2C_!INT!/6: J7.16, U19.C5
I2C_!INT!/7: J8.16, U22.C5
I2C_!INT!/8: J9.16, U25.C5
I2C_!INT!/9: J10.16, U28.C5
I2C_!INT!/10: J11.16, U31.C5
I2C_!INT!/11: J12.16, U34.C5
I2C_!INT!/12: J13.16, U37.C5
I2C_!INT!/13: J14.16, U40.C5
I2C_!INT!/29: J1.16, U1.C5
JTAG_MOD: U1.F13, U3.13
JTAG_MOD1: U4.F13, U6.13
JTAG_MOD2: U7.F13, U9.13
JTAG_MOD3: U10.F13, U12.13
JTAG_MOD4: U13.F13, U15.13
JTAG_MOD5: U16.F13, U18.13
JTAG_MOD6: U19.F13, U21.13
JTAG_MOD7: U22.F13, U24.13
JTAG_MOD8: U25.F13, U27.13
JTAG_MOD9: U28.F13, U30.13
JTAG_MOD10: U31.F13, U33.13
JTAG_MOD11: U34.F13, U36.13
JTAG_MOD12: U37.F13, U39.13
JTAG_MOD13: U40.F13, U42.13
JTAG_TCK: U1.F12, U3.8
JTAG_TCK1: U4.F12, U6.8
JTAG_TCK2: U7.F12, U9.8
JTAG_TCK3: U10.F12, U12.8
JTAG_TCK4: U13.F12, U15.8
JTAG_TCK5: U16.F12, U18.8
JTAG_TCK6: U19.F12, U21.8
JTAG_TCK7: U22.F12, U24.8
JTAG_TCK8: U25.F12, U27.8
JTAG_TCK9: U28.F12, U30.8
JTAG_TCK10: U31.F12, U33.8
JTAG_TCK11: U34.F12, U36.8
JTAG_TCK12: U37.F12, U39.8
JTAG_TCK13: U40.F12, U42.8
JTAG_TDI: U1.F14, U3.7
JTAG_TDI1: U4.F14, U6.7
JTAG_TDI2: U7.F14, U9.7
JTAG_TDI3: U10.F14, U12.7
JTAG_TDI4: U13.F14, U15.7
JTAG_TDI5: U16.F14, U18.7
JTAG_TDI6: U19.F14, U21.7
JTAG_TDI7: U22.F14, U24.7
JTAG_TDI8: U25.F14, U27.7
JTAG_TDI9: U28.F14, U30.7
JTAG_TDI10: U31.F14, U33.7
JTAG_TDI11: U34.F14, U36.7
JTAG_TDI12: U37.F14, U39.7
JTAG_TDI13: U40.F14, U42.7
JTAG_TDO: U1.G13, U3.6
JTAG_TDO1: U4.G13, U6.6
JTAG_TDO2: U7.G13, U9.6
JTAG_TDO3: U10.G13, U12.6
JTAG_TDO4: U13.G13, U15.6
JTAG_TDO5: U16.G13, U18.6
JTAG_TDO6: U19.G13, U21.6
JTAG_TDO7: U22.G13, U24.6
JTAG_TDO8: U25.G13, U27.6
JTAG_TDO9: U28.G13, U30.6
JTAG_TDO10: U31.G13, U33.6
JTAG_TDO11: U34.G13, U36.6
JTAG_TDO12: U37.G13, U39.6
JTAG_TDO13: U40.G13, U42.6
JTAG_TMS: U1.E14, U3.5
JTAG_TMS1: U4.E14, U6.5
JTAG_TMS2: U7.E14, U9.5
JTAG_TMS3: U10.E14, U12.5
JTAG_TMS4: U13.E14, U15.5
JTAG_TMS5: U16.E14, U18.5
JTAG_TMS6: U19.E14, U21.5
JTAG_TMS7: U22.E14, U24.5
JTAG_TMS8: U25.E14, U27.5
JTAG_TMS9: U28.E14, U30.5
JTAG_TMS10: U31.E14, U33.5
JTAG_TMS11: U34.E14, U36.5
JTAG_TMS12: U37.E14, U39.5
JTAG_TMS13: U40.E14, U42.5
JTAG_TRST: R5.2, U1.G10, U1.K3, U3.3
JTAG_TRST1: R8.2, U4.G10, U4.K3, U6.3
JTAG_TRST2: R13.2, U7.G10, U7.K3, U9.3
JTAG_TRST3: R18.2, U10.G10, U10.K3, U12.3
JTAG_TRST4: R23.2, U13.G10, U13.K3, U15.3
JTAG_TRST5: R28.2, U16.G10, U16.K3, U18.3
JTAG_TRST6: R33.2, U19.G10, U19.K3, U21.3
JTAG_TRST7: R38.2, U22.G10, U22.K3, U24.3
JTAG_TRST8: R43.2, U25.G10, U25.K3, U27.3
JTAG_TRST9: R48.2, U28.G10, U28.K3, U30.3
JTAG_TRST10: R53.2, U31.G10, U31.K3, U33.3
JTAG_TRST11: R58.2, U34.G10, U34.K3, U36.3
JTAG_TRST12: R63.2, U37.G10, U37.K3, U39.3
JTAG_TRST13: R68.2, U40.G10, U40.K3, U42.3
LRCLK/20/A1: J2.52, U4.L13
LRCLK/20/A2: J3.52, U7.L13
LRCLK/20/A3: J4.52, U10.L13
LRCLK/20/A4: J5.52, U13.L13
LRCLK/20/A5: J6.52, U16.L13
LRCLK/20/A6: J1.52, U1.L13
LRCLK/20/A7: J7.52, U19.L13
LRCLK/20/A8: J8.52, U22.L13
LRCLK/20/A9: J9.52, U25.L13
LRCLK/20/A10: J10.52, U28.L13
LRCLK/20/A11: J11.52, U31.L13
LRCLK/20/A12: J12.52, U34.L13
LRCLK/20/A13: J13.52, U37.L13
LRCLK/20/A14: J14.52, U40.L13
MCLK/23/A1: J2.58, U4.M13
MCLK/23/A2: J3.58, U7.M13
MCLK/23/A3: J4.58, U10.M13
MCLK/23/A4: J5.58, U13.M13
MCLK/23/A5: J6.58, U16.M13
MCLK/23/A6: J7.58, U19.M13
MCLK/23/A7: J8.58, U22.M13
MCLK/23/A8: J9.58, U25.M13
MCLK/23/A9: J1.58, U1.M13
MCLK/23/A10: J10.58, U28.M13
MCLK/23/A11: J11.58, U31.M13
MCLK/23/A12: J12.58, U34.M13
MCLK/23/A13: J13.58, U37.M13
MCLK/23/A14: J14.58, U40.M13
MISO/1: J2.61, U4.E7
MISO/2: J3.61, U7.E7
MISO/3: J4.61, U10.E7
MISO/4: J5.61, U13.E7
MISO/5: J6.61, U16.E7
MISO/6: J7.61, U19.E7
MISO/7: J8.61, U22.E7
MISO/8: J9.61, U25.E7
MISO/9: J10.61, U28.E7
MISO/10: J11.61, U31.E7
MISO/11: J12.61, U34.E7
MISO/12: J1.61, U1.E7
MISO/13: J13.61, U37.E7
MISO/14: J14.61, U40.E7
MOSI/1: J2.59, U4.E8
MOSI/2: J3.59, U7.E8
MOSI/3: J4.59, U10.E8
MOSI/4: J5.59, U13.E8
MOSI/5: J6.59, U16.E8
MOSI/6: J7.59, U19.E8
MOSI/7: J8.59, U22.E8
MOSI/8: J9.59, U25.E8
MOSI/9: J10.59, U28.E8
MOSI/10: J11.59, U31.E8
MOSI/11: J1.59, U1.E8
MOSI/12: J12.59, U34.E8
MOSI/13: J13.59, U37.E8
MOSI/14: J14.59, U40.E8
unnamed: TP1.P$1, U1.M14
unnamed: D1.A, R1.1
unnamed: C10.1, C14.1, C15.1, FB2.2, U1.L1, U1.L2
unnamed: C7.1, U1.N11, Y2.3
unnamed: C6.1, R4.2, U1.P11, Y2.1
unnamed: C35.1, U4.P9, Y3.P$2
unnamed: C34.1, U4.N9, Y3.P$1
unnamed: TP2.P$1, U4.M14
unnamed: L2.1, U1.M1, U1.M2
unnamed: C11.1, FB1.1, MEAS.2
unnamed: D6.A, R2.1
unnamed: R7.1, U3.11
unnamed: D5.C, R7.2
unnamed: C37.1, U4.N11, Y4.3
unnamed: C36.1, R3.2, U4.P11, Y4.1
unnamed: C38.1, C42.1, C43.1, FB4.2, U4.L1, U4.L2
unnamed: L1.1, U4.M1, U4.M2
unnamed: C51.1, TP14.P$1, U4.M10
unnamed: C52.1, C54.1, TP15.P$1, U4.P10
unnamed: C53.1, C55.1, TP16.P$1, U4.P8
unnamed: R10.1, U6.11
unnamed: D10.C, R10.2
unnamed: C39.1, FB3.1, MEAS1.2
unnamed: C63.1, U7.P9, Y5.P$2
unnamed: C62.1, U7.N9, Y5.P$1
unnamed: TP21.P$1, U7.M14
unnamed: D11.A, R11.1
unnamed: C65.1, U7.N11, Y6.3
unnamed: C64.1, R12.2, U7.P11, Y6.1
unnamed: C23.1, TP5.P$1, U1.M10
unnamed: C9.1, U1.P9, Y1.P$2
unnamed: C8.1, U1.N9, Y1.P$1
unnamed: C24.1, C26.1, TP6.P$1, U1.P10
unnamed: C25.1, C27.1, TP7.P$1, U1.P8
unnamed: C66.1, C70.1, C71.1, FB6.2, U7.L1, U7.L2
unnamed: L3.1, U7.M1, U7.M2
unnamed: C79.1, TP24.P$1, U7.M10
unnamed: C80.1, C82.1, TP25.P$1, U7.P10
unnamed: C81.1, C83.1, TP26.P$1, U7.P8
unnamed: R15.1, U9.11
unnamed: D15.C, R15.2
unnamed: C67.1, FB5.1, MEAS2.2
unnamed: C91.1, U10.P9, Y7.P$2
unnamed: C90.1, U10.N9, Y7.P$1
unnamed: TP31.P$1, U10.M14
unnamed: D16.A, R16.1
unnamed: C93.1, U10.N11, Y8.3
unnamed: C92.1, R17.2, U10.P11, Y8.1
unnamed: C94.1, C98.1, C99.1, FB8.2, U10.L1, U10.L2
unnamed: L4.1, U10.M1, U10.M2
unnamed: C107.1, TP34.P$1, U10.M10
unnamed: C108.1, C110.1, TP35.P$1, U10.P10
unnamed: C109.1, C111.1, TP36.P$1, U10.P8
unnamed: R20.1, U12.11
unnamed: D20.C, R20.2
unnamed: C95.1, FB7.1, MEAS3.2
unnamed: C119.1, U13.P9, Y9.P$2
unnamed: C118.1, U13.N9, Y9.P$1
unnamed: TP41.P$1, U13.M14
unnamed: D21.A, R21.1
unnamed: C121.1, U13.N11, Y10.3
unnamed: C120.1, R22.2, U13.P11, Y10.1
unnamed: C122.1, C126.1, C127.1, FB10.2, U13.L1, U13.L2
unnamed: L5.1, U13.M1, U13.M2
unnamed: C135.1, TP44.P$1, U13.M10
unnamed: C136.1, C138.1, TP45.P$1, U13.P10
unnamed: C137.1, C139.1, TP46.P$1, U13.P8
unnamed: R25.1, U15.11
unnamed: D25.C, R25.2
unnamed: C123.1, FB9.1, MEAS4.2
unnamed: C147.1, U16.P9, Y11.P$2
unnamed: C146.1, U16.N9, Y11.P$1
unnamed: TP51.P$1, U16.M14
unnamed: D26.A, R26.1
unnamed: C149.1, U16.N11, Y12.3
unnamed: C148.1, R27.2, U16.P11, Y12.1
unnamed: C150.1, C154.1, C155.1, FB12.2, U16.L1, U16.L2
unnamed: L6.1, U16.M1, U16.M2
unnamed: C163.1, TP54.P$1, U16.M10
unnamed: C164.1, C166.1, TP55.P$1, U16.P10
unnamed: C165.1, C167.1, TP56.P$1, U16.P8
unnamed: R30.1, U18.11
unnamed: D30.C, R30.2
unnamed: C151.1, FB11.1, MEAS5.2
unnamed: C175.1, U19.P9, Y13.P$2
unnamed: C174.1, U19.N9, Y13.P$1
unnamed: TP61.P$1, U19.M14
unnamed: D31.A, R31.1
unnamed: C177.1, U19.N11, Y14.3
unnamed: C176.1, R32.2, U19.P11, Y14.1
unnamed: C178.1, C182.1, C183.1, FB14.2, U19.L1, U19.L2
unnamed: L7.1, U19.M1, U19.M2
unnamed: C191.1, TP64.P$1, U19.M10
unnamed: C192.1, C194.1, TP65.P$1, U19.P10
unnamed: C193.1, C195.1, TP66.P$1, U19.P8
unnamed: R35.1, U21.11
unnamed: D35.C, R35.2
unnamed: C179.1, FB13.1, MEAS6.2
unnamed: C203.1, U22.P9, Y15.P$2
unnamed: C202.1, U22.N9, Y15.P$1
unnamed: TP71.P$1, U22.M14
unnamed: D36.A, R36.1
unnamed: C205.1, U22.N11, Y16.3
unnamed: C204.1, R37.2, U22.P11, Y16.1
unnamed: C206.1, C210.1, C211.1, FB16.2, U22.L1, U22.L2
unnamed: L8.1, U22.M1, U22.M2
unnamed: C219.1, TP74.P$1, U22.M10
unnamed: C220.1, C222.1, TP75.P$1, U22.P10
unnamed: C221.1, C223.1, TP76.P$1, U22.P8
unnamed: R40.1, U24.11
unnamed: D40.C, R40.2
unnamed: C207.1, FB15.1, MEAS7.2
unnamed: C231.1, U25.P9, Y17.P$2
unnamed: C230.1, U25.N9, Y17.P$1
unnamed: TP81.P$1, U25.M14
unnamed: D41.A, R41.1
unnamed: C233.1, U25.N11, Y18.3
unnamed: C232.1, R42.2, U25.P11, Y18.1
unnamed: C234.1, C238.1, C239.1, FB18.2, U25.L1, U25.L2
unnamed: L9.1, U25.M1, U25.M2
unnamed: C247.1, TP84.P$1, U25.M10
unnamed: C248.1, C250.1, TP85.P$1, U25.P10
unnamed: C249.1, C251.1, TP86.P$1, U25.P8
unnamed: R45.1, U27.11
unnamed: D45.C, R45.2
unnamed: C235.1, FB17.1, MEAS8.2
unnamed: C259.1, U28.P9, Y19.P$2
unnamed: C258.1, U28.N9, Y19.P$1
unnamed: TP91.P$1, U28.M14
unnamed: D46.A, R46.1
unnamed: C261.1, U28.N11, Y20.3
unnamed: C260.1, R47.2, U28.P11, Y20.1
unnamed: C262.1, C266.1, C267.1, FB20.2, U28.L1, U28.L2
unnamed: L10.1, U28.M1, U28.M2
unnamed: C275.1, TP94.P$1, U28.M10
unnamed: C276.1, C278.1, TP95.P$1, U28.P10
unnamed: C277.1, C279.1, TP96.P$1, U28.P8
unnamed: R50.1, U30.11
unnamed: D50.C, R50.2
unnamed: C263.1, FB19.1, MEAS9.2
unnamed: C287.1, U31.P9, Y21.P$2
unnamed: C286.1, U31.N9, Y21.P$1
unnamed: TP101.P$1, U31.M14
unnamed: D51.A, R51.1
unnamed: C289.1, U31.N11, Y22.3
unnamed: C288.1, R52.2, U31.P11, Y22.1
unnamed: C290.1, C294.1, C295.1, FB22.2, U31.L1, U31.L2
unnamed: L11.1, U31.M1, U31.M2
unnamed: C303.1, TP104.P$1, U31.M10
unnamed: C304.1, C306.1, TP105.P$1, U31.P10
unnamed: C305.1, C307.1, TP106.P$1, U31.P8
unnamed: R55.1, U33.11
unnamed: D55.C, R55.2
unnamed: C291.1, FB21.1, MEAS10.2
unnamed: C315.1, U34.P9, Y23.P$2
unnamed: C314.1, U34.N9, Y23.P$1
unnamed: TP111.P$1, U34.M14
unnamed: D56.A, R56.1
unnamed: C317.1, U34.N11, Y24.3
unnamed: C316.1, R57.2, U34.P11, Y24.1
unnamed: C318.1, C322.1, C323.1, FB24.2, U34.L1, U34.L2
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
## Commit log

2020-03-21 Add production files
2020-03-21 Add docs. Add lib.
2020-03-21 v11 PCB. Fix connection to DCDC_SENSE.
2020-03-23 Routed with 5mil. Increased clk spacing.
2020-03-24 Breakout PMIC. Reduce beads to 0402T.
2020-03-24 Rearrange UART pins
2020-03-27 Add power control circuitry.
2020-03-27 Adding panel files
2020-03-27 Remove cream from test points
2020-04-01 Matches trace lenths to flash. New panel.
2020-04-04 Route bus pins to v11.
2020-04-14 Add ordering instructions
2020-04-14 Update Micromod connector to current version
2020-04-15 Adding test point measurements
2020-05-14 Add 3.3V EN. Increase flash IC size to 6x5mm.
2020-05-14 Move a few vias from BGA pads.
2020-05-14 Move via away from BGA
2020-05-14 Move via away from ball.
2020-05-18 Reroute 3.3V_EN to available standard GPIO 28. Adjust R4 for more space.
2020-05-19 Adjust inductor position. Change MM logo.
2020-05-19 v12 production files
2020-06-09 Add PROD_IDs to 120ohm ferrite
2020-06-19 Fix DAT2/DAT3, now correctly connected to B0_04 and B0_05.
2020-06-19 Fix incorrect SDA/SCL1 board edge connector pinout
2020-06-23 Update copper to v13. Add production files.
2020-08-21 Remove traces from beneath xtals.
2020-08-24 Switch layers 2/15 to put ground under xtals. Increase GND plane on layer 15.
2020-08-24 Increase TP size and relocate to more open areas
2020-08-24 High freq trace length matching
2020-08-24 Opening layer 2 for better GND connections
2020-08-25 Moved test-points for ideal testing
2020-08-25 Connect 3.3V_Controlled to peripherals. Increase internal power trace widths.
2020-08-26 moved some TP's around to get clearence for pogopins
2020-08-26 Production v14 panel and gerber files
2020-08-26 Incorporate TP changes
2020-08-27 DFM changes: move traces to avoid t/b stop exposure
2020-08-28 Adding production panel files
2020-08-29 Move trace away from top edge
2020-08-31 Move trace away from edge to pass DFM requirements
2020-10-01 Update SPI0 net names.
2020-10-19 Create README
    Initial README commit.
2020-10-19 Add designed by text on PCB
2021-04-19 Add ENIG finish note.
2021-04-19 Add panel files for v15 with ENIG finish notes
2021-04-19 Re-add v15 panel files
2021-04-19 Add beveled edge note to instructions
2021-07-02 Fix bad links in readme
2021-09-21 Adding lockable version of PCB
2021-11-03 Correct swapped pin numbers on DAT2/3.
    This stems from an error in the original Teensy 4.0 schematic. It was found and corrected but Paul swapped the pin numbers where we swapped the net names. This should get us back on the same page.
2023-05-16 Revert "Correct swapped pin numbers on DAT2/3."
    This reverts commit 18efc8621dbd46baebb258ee20b759296ca70ac1.
    Pin swap was fixed in software: https://github.com/PaulStoffregen/cores/commit/17f652645c1af3bb0190d6b3769d48358c7ad276
